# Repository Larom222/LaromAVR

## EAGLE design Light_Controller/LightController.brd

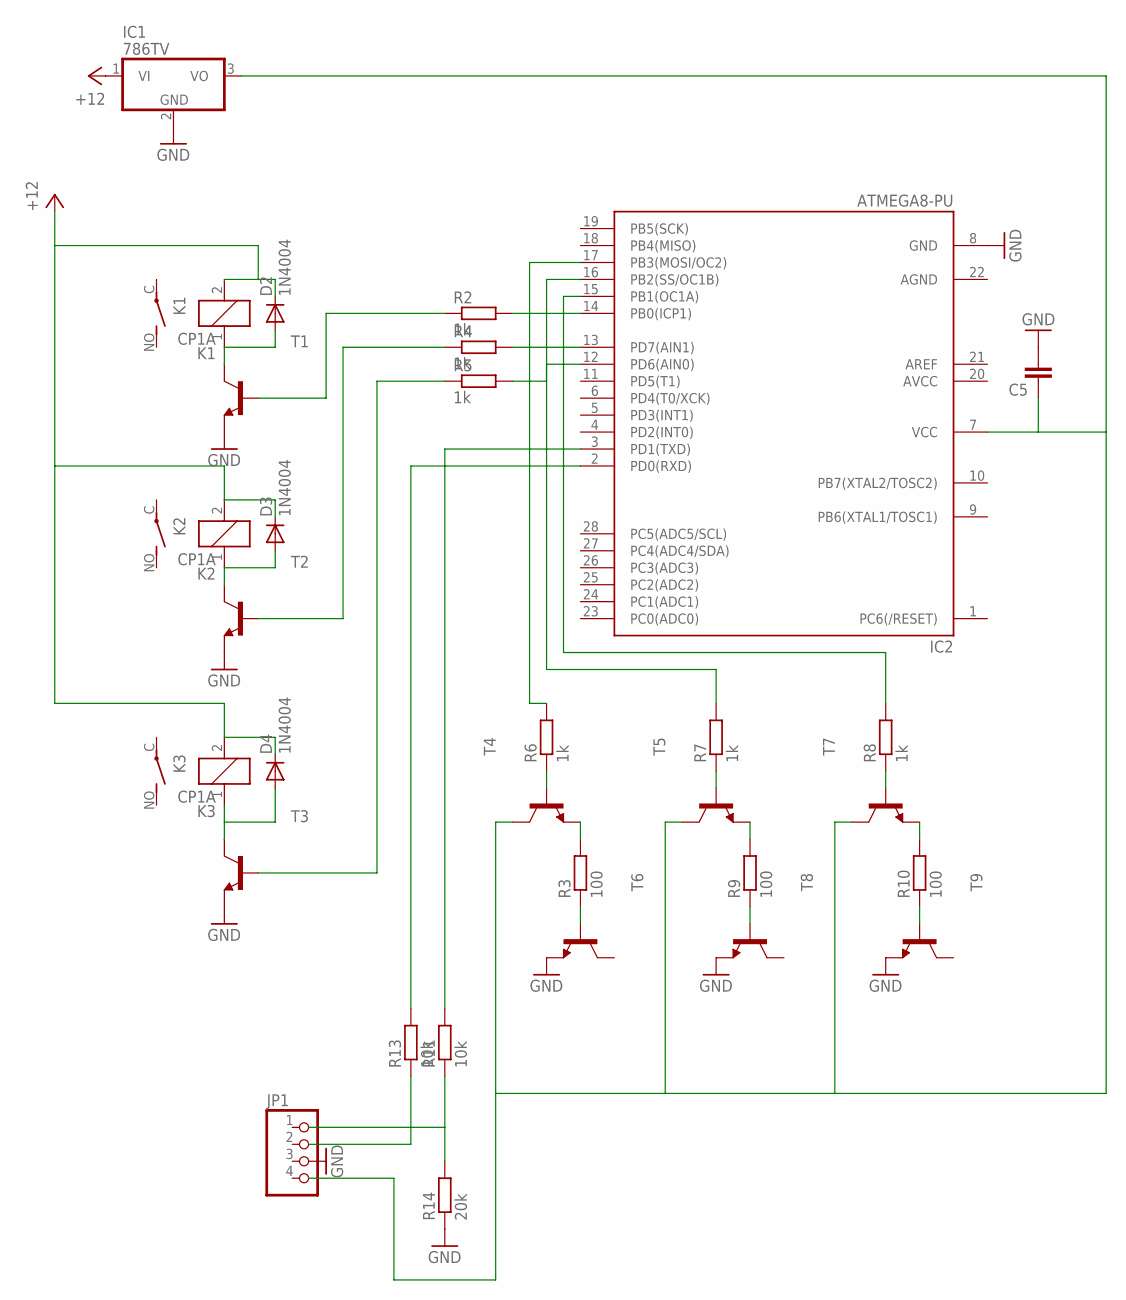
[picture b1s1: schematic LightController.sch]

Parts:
C5: C2,5-3; C2.5-3
D2, D3, D4: 1N4004; DO41-10
IC1: 786TV; TO220V
IC2: ATMEGA8-PU; DIL28-3
JP1: PINHD-1X4; 1X04
K1, K2, K3: CP1A
R2, R4, R5, R6, R7, R8: 1k; 0204/7
R3, R9, R10: 100; 0204/7
R11, R13: 10k; 0204/7
R14: 20k; 0204/7
T1, T2, T3, T4, T5, T7: -NPN-TO92-EBC; TO92-EBC
T6, T8, T9: BF420-NPN-TO92-BCE; TO92-BCE

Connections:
AGND: IC2.22 (AGND)
GND: C5.2, IC1.2 (GND), IC2.8 (GND), R14.1, T1.E, T2.E, T3.E, T6.E, T8.E, T9.E
unnamed: IC2.15 (PB1(OC1A)), R8.2
unnamed: IC2.16 (PB2(SS/OC1B)), R7.2
unnamed: R3.2, T4.E
unnamed: D2.A, K1.1, T1.C
unnamed: IC2.14 (PB0(ICP1)), R2.2
unnamed: R2.1, T1.B
unnamed: R4.1, T2.B
unnamed: D4.A, K3.1, T3.C
unnamed: D3.A, K2.1, T2.C
unnamed: IC2.13 (PD7(AIN1)), R4.2
unnamed: R5.1, T3.B
unnamed: IC2.12 (PD6(AIN0)), R5.2
unnamed: IC2.17 (PB3(MOSI/OC2)), R6.2
unnamed: R3.1, T6.B
unnamed: R9.2, T5.E
unnamed: R9.1, T8.B
unnamed: R10.2, T7.E
unnamed: R10.1, T9.B
unnamed: R6.1, T4.B
unnamed: R7.1, T5.B
unnamed: R8.1, T7.B
unnamed: IC2.2 (PD0(RXD)), R13.2
unnamed: R11.1, R14.2
unnamed: IC2.3 (PD1(TXD)), R11.2
unnamed: C5.1, IC1.3 (VO), IC2.7 (VCC), T4.C, T5.C, T7.C
VCC: D2.C, D3.C, D4.C, IC1.1 (VI), K1.2, K2.2, K3.2

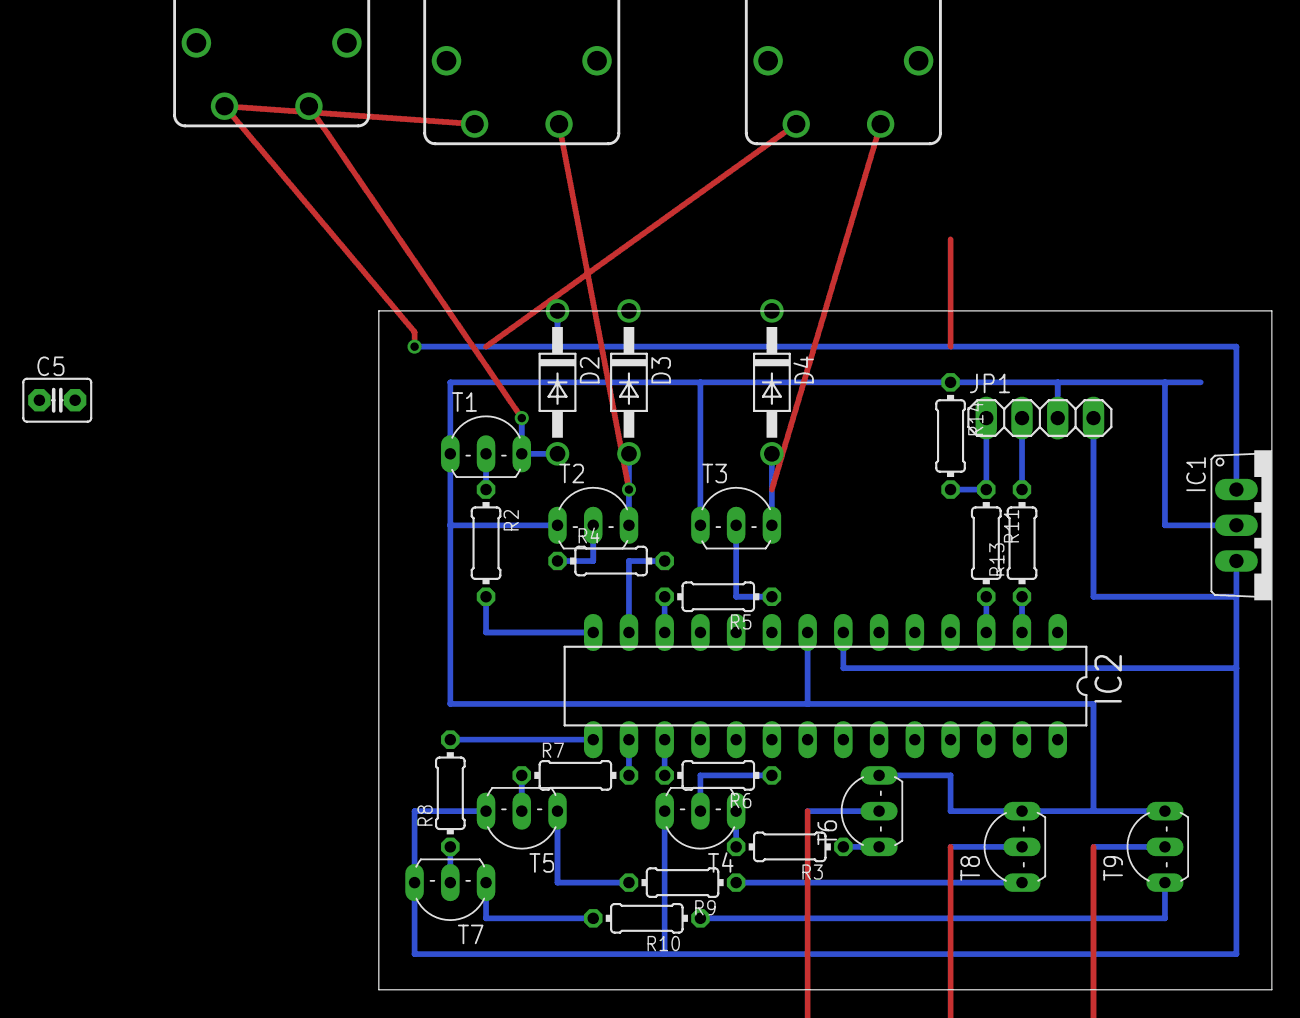
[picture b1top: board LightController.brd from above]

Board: 2 copper layers, 63.5 x 48.3 mm, 31 parts (0 on the bottom side), 27 nets.

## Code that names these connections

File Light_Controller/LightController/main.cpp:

/*
 * LightController.cpp
 *
 * Created: 2020-05-29 20:40:12
 * Author : Gabriel
 */ 

#define F_CPU 8000000

#include <avr/io.h>
#include <avr/interrupt.h>
#include <util/delay.h>

//#include "../../_Libraries/LCD_Display/LCD_Display.h"

enum E_RX_STATE
{
	RXS_STX = 0,
	RXS_ETX = 1,
};

unsigned char RxBuf[6];
unsigned char ReadBuf[4];
unsigned char RxBufPos = 0;
unsigned char RxState = RXS_STX;
unsigned char PWM = 0;
bool readyToRead = false;

unsigned char lightR = 0;
unsigned char lightG = 0;
unsigned char lightB = 0;

unsigned long long ms = 0;

bool haloState = false;
bool light1State = false;
bool light2State = false;
bool light3State = false;

#define ATMEGA8
void ConfigUART()
{
	cli();
	
#ifdef ATMEGA328P
	UBRR0H=0x00;
	UBRR0L=51;
	
	
	//---------------------------
	UCSR0B=0x00;
	UCSR0B|=0x80 | 0x10 | 0x08;     //Rx przerwania on, rx enable, tx enalbe
	//---------------------------
	UCSR0C=0x00;                    // tryb asynchroniczny, bez przystosci, 1 bit stopu
	UCSR0C|=0x04 | 0x02;            // 8 date bits
#else
#define BAUD_PRESCALE (((8000000 / (9600 * 16UL))) - 1) 
	UBRRH= BAUD_PRESCALE >> 8;
	UBRRL= BAUD_PRESCALE;

//UCSRA bez zmian - 0x00
	UCSRA = 0x00;
	UCSRB = (1<<RXCIE)|(1<<RXEN)|(1<<TXEN);                 //aktywne przerwanie od odbioru oraz zmiana trybu dzia³ania pinów D0 i D1
	UCSRC = (1 << URSEL) | (1 << UCSZ0) | (1 << UCSZ1);     //praca synchroniczna, brak kontroli parzystoci, 1 bit stopu, 8 bitów danych

/*
	UCSRA=0x00;
	//---------------------------
	UCSRB=0x00;
	UCSRB|=0x80 | 0x10 | 0x08;     //Rx przerwania on, rx enable, tx enalbe
	//---------------------------
	UCSRC=0x00;                    // tryb asynchroniczny, bez przystosci, 1 bit stopu
	UCSRC|=0x04 | 0x02;            // 8 date bits*/
#endif
	
	sei();
}

void ConfigurePWM()
{
	cli();
	
	//TCCR1A |= (1 << WGM11);	// Set the Timer Mode to CTC
	//TIMSK1 |= (1 << OCIE1A);
	//TCCR1B |= (1 << CS10); // timer1 prescaler = 8
	//OCR1A = 0x90; //interrupt every 50us
	
	
	
	OCR1A = 0x0100;

	TCCR1B |= (1 << WGM12);
	// Mode 4, CTC on OCR1A
#ifdef ATMEGA328P
	TIMSK1 |= (1 << OCIE1A);
	//Set interrupt on compare match
#else
	TIMSK |= (1 << OCIE1A);
	//Set interrupt on compare match
#endif

	TCCR1B |= (1 << CS10);
	// set prescaler to 1024 and start the timer


	sei();
	// enable interrupts
	
	
	
	//sei();
};

int main(void)
{
	DDRB |= (1 << PB0); //PB0 as output
	DDRD |= (1 << PD6); //PD6 as output
	DDRD |= (1 << PD7); //PD7 as output
	DDRB |= (1 << PB1); //PB1 as output
	DDRB |= (1 << PB2); //PB2 as output
	DDRB |= (1 << PB3); //PB3 as output
	DDRD |= (1 << PD5); //PB3 as output
	
	PORTD &= ~(1 << PD7);
	PORTD &= ~(1 << PD6);
	PORTB &= ~(1 << PB0);
	PORTD &= ~(1 << PD5);
	
	PORTB &= ~(1 << PB1);
	PORTB &= ~(1 << PB2);
	PORTB &= ~(1 << PB3);
	
	ConfigUART();
	ConfigurePWM();
	
	//DisplayLCD::GetInstance().Initialize();
	
    /* Replace with your application code */
    while (true) 
    {				
		_delay_ms(1);			
		if(readyToRead)
		{
			readyToRead = false;
			unsigned char buf = 0;
			
			if(ReadBuf[0] == 'R' || ReadBuf[0] == 'G' || ReadBuf[0] == 'B')
			{				
				buf += ReadBuf[3] - 48;
				buf += (ReadBuf[2] - 48) * 10;
				buf += (ReadBuf[1] - 48) * 100;
			}
			
			switch(ReadBuf[0])
			{
				case 'R':
					if(buf > 255)
						break;
					lightR = buf;
					break;
				case 'G':
					if(buf > 255)
						break;
					lightG = buf;
					break;
				case 'B':
					if(buf > 255)
						break;
					lightB = buf;
					break;
				case '1':
					if(haloState)
					{
						haloState = false;
						PORTB &= ~(1 << PB0);
					}
					else
					{
						haloState = true;
						PORTB |= (1 << PB0);
					}
					break;
				case '2':
					if(light1State)
					{
						light1State = false;
						PORTD &= ~(1 << PD7);
					}
					else
					{
						light1State = true;
						PORTD |= (1 << PD7);
					}
					break;
				case '3':
					if(light2State)
					{
						light2State = false;
						PORTD &= ~(1 << PD6);
					}
					else
					{
						light2State = true;
						PORTD |= (1 << PD6);
					}
					break;
				case '4':
					if(light3State)
					{
						light3State = false;
						PORTD &= ~(1 << PD5);
					}
					else
					{
						light3State = true;
						PORTD |= (1 << PD5);
					}
					break;
			}
		}
		/*if(DisplayLCD::GetInstance().GetAvailableTextLength() > 6)
		{
			char buf[6];
			buf[5] = ms % 10 + 48;
			buf[4] = (ms / 10) % 10 + 48;
			buf[3] = (ms / 100) % 10 + 48;
			buf[2] = (ms / 1000) % 10 + 48;
			buf[1] = (ms / 10000) % 10 + 48;
			buf[0] = (ms / 100000) % 10 + 48;
			DisplayLCD::GetInstance().WriteText(buf, FIRST_LINE_ADDRESS, 6);
		}
		DisplayLCD::GetInstance().Process();*/
    }
}

ISR (TIMER1_COMPA_vect)
{
	++PWM;
	if(PWM > lightR || lightR == 0)
		PORTB &= ~(1 << PB1);
	else
		PORTB |= (1 << PB1);
		
	if(PWM > lightG || lightG == 0)
		PORTB &= ~(1 << PB2);
	else
		PORTB |= (1 << PB2);
		
	if(PWM > lightB || lightB == 0)
		PORTB &= ~(1 << PB3);
	else
		PORTB |= (1 << PB3);
	++ms;
}

#ifdef ATMEGA328P
ISR(USART_RX_vect)
#else
ISR(USART_RXC_vect)
#endif
{
	unsigned char data;
#ifdef ATMEGA328P
	data = UDR0;
#else
	data = UDR;
#endif
	
	if(RxState == RXS_STX)
	{		
		if(data == 2)
		{			
			RxBuf[0] = data;
			RxBufPos = 1;
			RxState = RXS_ETX;
		}		
	}
	else if(RxState == RXS_ETX)
	{
		RxBuf[RxBufPos] = data;
		RxBufPos++;
		if(data == 3)
		{
			RxState = RXS_STX;
			readyToRead = true;			
			for(int i = 0; i < 4; i++)
			{
				ReadBuf[i] = RxBuf[i + 1];
			}
		}
	}
}

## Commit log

2020-02-23 Added libraries Added Temperature regulator project
2020-02-23 Added all existing projects
2020-02-23 Temperature regulator implementation
2020-02-23 Fixed TWI crash after time or temperature update
2020-03-08 Added sound manager
2020-05-17 Fixed datetime saving
2020-06-19 Added LightController and HC_06_TEST projects
